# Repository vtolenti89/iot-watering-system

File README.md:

# IoT Watering System
Automated low power watering system 

# Overview
This project aims to automate a watering system for a small garden.
Due to the lack of an outside spigot / outdoor faucet, a large 
reservoir and an intermediate container were used to store the water,
which then was pumped to the plants at a regular interval using
an arduino controlled pump.  

# Description
The larger reservoir ensures that there is enough water for a resonable time.
Pumping the water to an intermediate container, alleviates the requirement
for the water pump, since it does not have to force the water through the end
nozzles. In this arrangement, gravity will ensure that the water is evenly 
distributed through all of them.
A homemade ruler sensor is used to measure the water level of the main tank,
while the smaller container's sensor prevents any overflow. 

# TODO
* Implement the display
* Implement again wifi with low power option

# History
* Implement a second code version, where the wifi is disabled and the power consumption is drastically
reduced by hardware modification and use of deep sleep routines
* Implement first version with wifi

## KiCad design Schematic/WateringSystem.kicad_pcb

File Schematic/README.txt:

Several features of the current schematic were removed / disabled in order to improve the power consumption
Changes implemented in the arduino:

1. LDO removed, thus external supply voltage other than the USB is not possible
2. Apart from the built-in LED, all other LEDs were removed.
3. Supply voltage of the CH340 was removed

Changes implemented in the peripheral circuitry:

1. ESP8266 WIfi module removed
2. Water level meter disabled

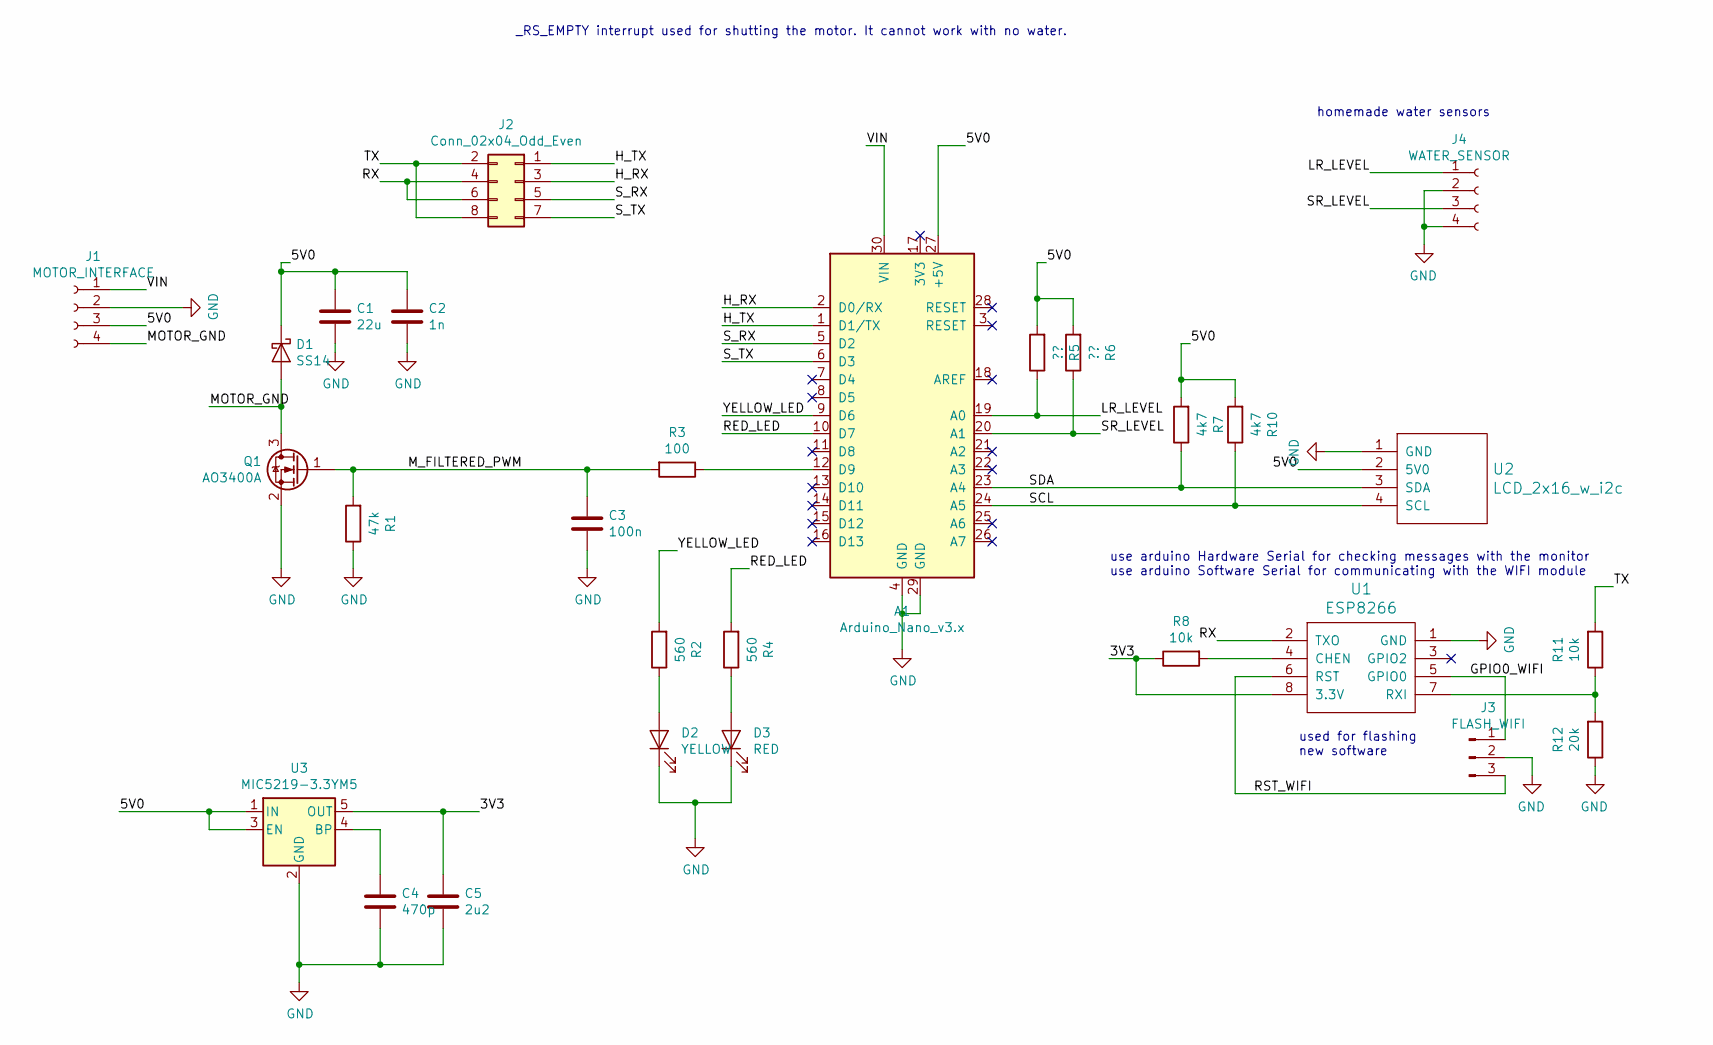
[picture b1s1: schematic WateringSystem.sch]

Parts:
A1: Arduino_Nano_v3.x; Arduino_Nano_WithMountingHoles
C1: 22u; C_0603_1608Metric_Pad1.05x0.95mm_HandSolder
C2: 1n; C_0603_1608Metric_Pad1.05x0.95mm_HandSolder
C3: 100n; C_0603_1608Metric_Pad1.05x0.95mm_HandSolder
C4: 470p; C_0603_1608Metric_Pad1.05x0.95mm_HandSolder
C5: 2u2; C_0603_1608Metric_Pad1.05x0.95mm_HandSolder
D1: SS14; SMA_DO-214AC
D2: YELLOW; LED_1206_3216Metric_Pad1.42x1.75mm_HandSolder
D3: RED; LED_1206_3216Metric_Pad1.42x1.75mm_HandSolder
J1: MOTOR_INTERFACE; PinHeader_1x04_P2.54mm_Vertical
J2: Conn_02x04_Odd_Even; PinHeader_2x04_P2.54mm_Vertical
J3: FLASH_WIFI; PinHeader_1x03_P2.54mm_Vertical
J4: WATER_SENSOR; PinHeader_1x04_P2.54mm_Vertical
Q1: AO3400A; SOT-23
R1: 47k; R_0603_1608Metric_Pad1.05x0.95mm_HandSolder
R2, R4: 560; R_0603_1608Metric_Pad1.05x0.95mm_HandSolder
R3: 100; R_0603_1608Metric_Pad1.05x0.95mm_HandSolder
R5, R6: ??; R_0603_1608Metric_Pad1.05x0.95mm_HandSolder
R7, R10: 4k7; R_0603_1608Metric_Pad1.05x0.95mm_HandSolder
R8, R11: 10k; R_0603_1608Metric_Pad1.05x0.95mm_HandSolder
R12: 20k; R_0603_1608Metric_Pad1.05x0.95mm_HandSolder
U1: ESP8266; PinHeader_2x04_P2.54mm_Vertical
U2: LCD_2x16_w_i2c; PinHeader_1x04_P2.54mm_Vertical
U3: MIC5219-3.3YM5; SOT-23-5

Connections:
/3V3: C5.1, R8.1, U1.8 (3.3V), U3.5 (OUT)
/5V0: A1.27 (+5V), C1.1, C2.1, D1.1 (K), J1.3, R5.2, R6.2, R7.2, R10.2, U2.2 (5V0), U3.1 (IN), U3.3 (EN)
/GPIO0_WIFI: J3.1, U1.5 (GPIO0)
/H_RX: A1.2 (D0/RX), J2.3
/H_TX: A1.1 (D1/TX), J2.1
/LR_LEVEL: A1.19 (A0), J4.1, R5.1
/MOTOR_GND: D1.2 (A), J1.4, Q1.3 (D)
/M_FILTERED_PWM: C3.1, Q1.1 (G), R1.2, R3.2
/RED_LED: A1.10 (D7), R4.2
/RST_WIFI: J3.3, U1.6 (RST)
/RX: J2.4, J2.6, U1.2 (TXO)
/SCL: A1.24 (A5), R10.1, U2.4 (SCL)
/SDA: A1.23 (A4), R7.1, U2.3 (SDA)
/SR_LEVEL: A1.20 (A1), J4.3, R6.1
/S_RX: A1.5 (D2), J2.5
/S_TX: A1.6 (D3), J2.7
/TX: J2.2, J2.8, R11.2
/VIN: A1.30 (VIN), J1.1
/YELLOW_LED: A1.9 (D6), R2.2
GND: A1.4 (GND), A1.29 (GND), C1.2, C2.2, C3.2, C4.2, C5.2, D2.1 (K), D3.1 (K), J1.2, J3.2, J4.2, J4.4, Q1.2 (S), R1.1, R12.1, U1.1 (GND), U2.1 (GND), U3.2 (GND)
unnamed: A1.12 (D9), R3.1
unnamed: C4.1, U3.4 (BP)
unnamed: D2.2 (A), R2.1
unnamed: D3.2 (A), R4.1
unnamed: R8.2, U1.4 (CHEN)
unnamed: R11.1, R12.2, U1.7 (RXI)

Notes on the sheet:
use arduino Hardware Serial for checking messages with the monitor use arduino Software Serial for communicating with the WIFI module
_RS_EMPTY interrupt used for shutting the motor. It cannot work with no water.
used for flashing new software
homemade water sensors

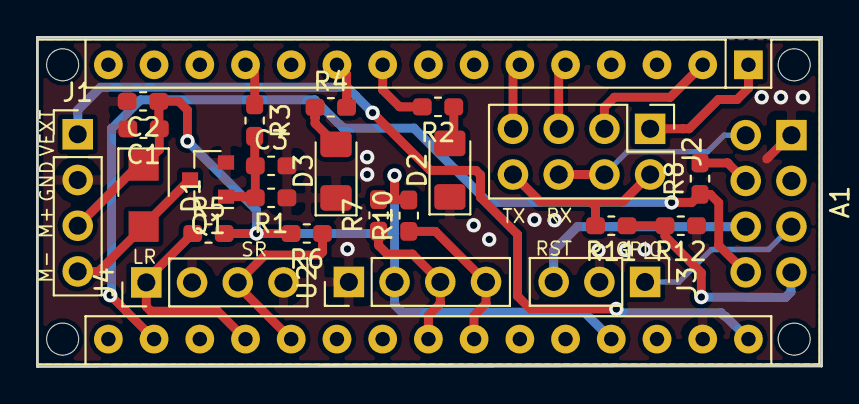
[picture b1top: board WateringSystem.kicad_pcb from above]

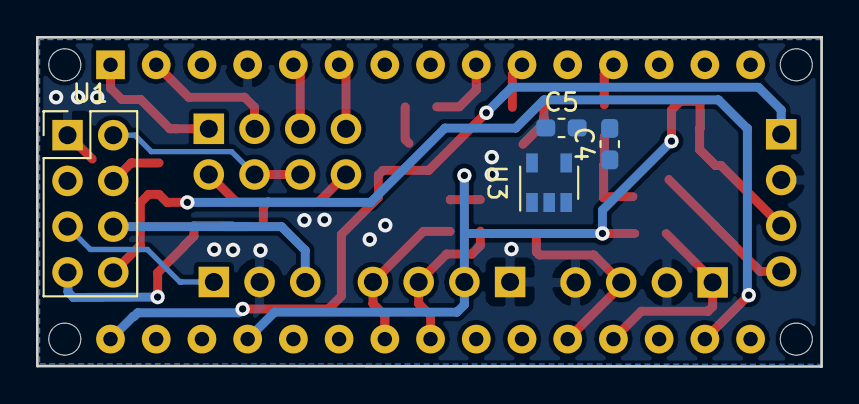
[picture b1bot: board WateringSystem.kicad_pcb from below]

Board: 2 copper layers, 43.6 x 18.3 mm, 28 parts (4 on the bottom side), 26 nets.

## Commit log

2020-05-17 add block diagram
2020-05-29 update low power software
2020-09-08 update master
